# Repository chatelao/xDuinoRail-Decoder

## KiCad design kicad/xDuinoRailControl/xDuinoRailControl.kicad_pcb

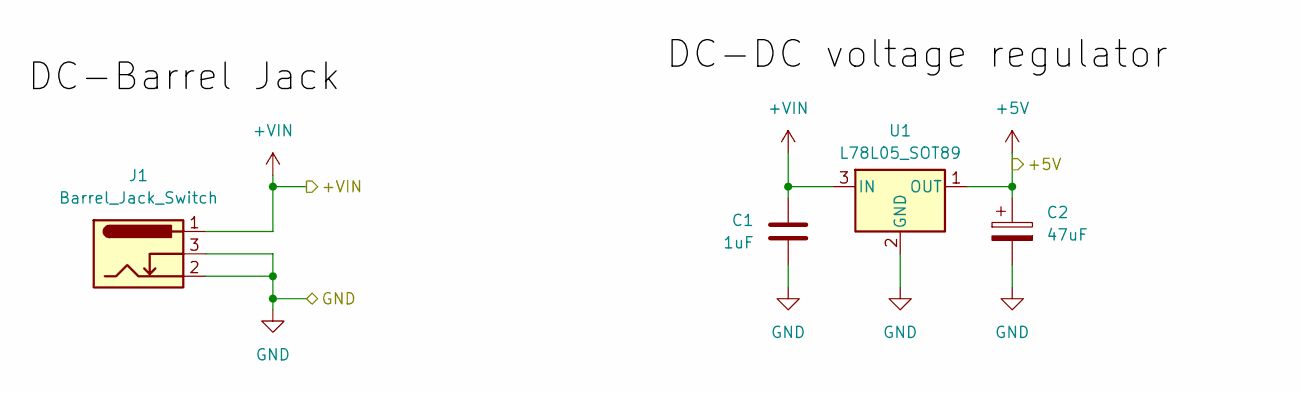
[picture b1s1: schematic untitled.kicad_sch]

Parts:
C1: 1uF; C_0805_2012Metric_Pad1.18x1.45mm_HandSolder; LCSC C28323
C2: 47uF; C_0805_2012Metric_Pad1.18x1.45mm_HandSolder; LCSC C16780
J1: Barrel_Jack_Switch; BarrelJack_Wuerth_6941xx301002; LCSC C431532
U1: L78L05_SOT89; SOT-89-3; LCSC C71136

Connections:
+3V3: C2.1, U1.1 (OUT); also elsewhere on the board
+VIN: C1.1, J1.1, U1.3 (IN); also elsewhere on the board
GND: C1.2, C2.2, J1.2, J1.3, U1.2 (GND); also elsewhere on the board

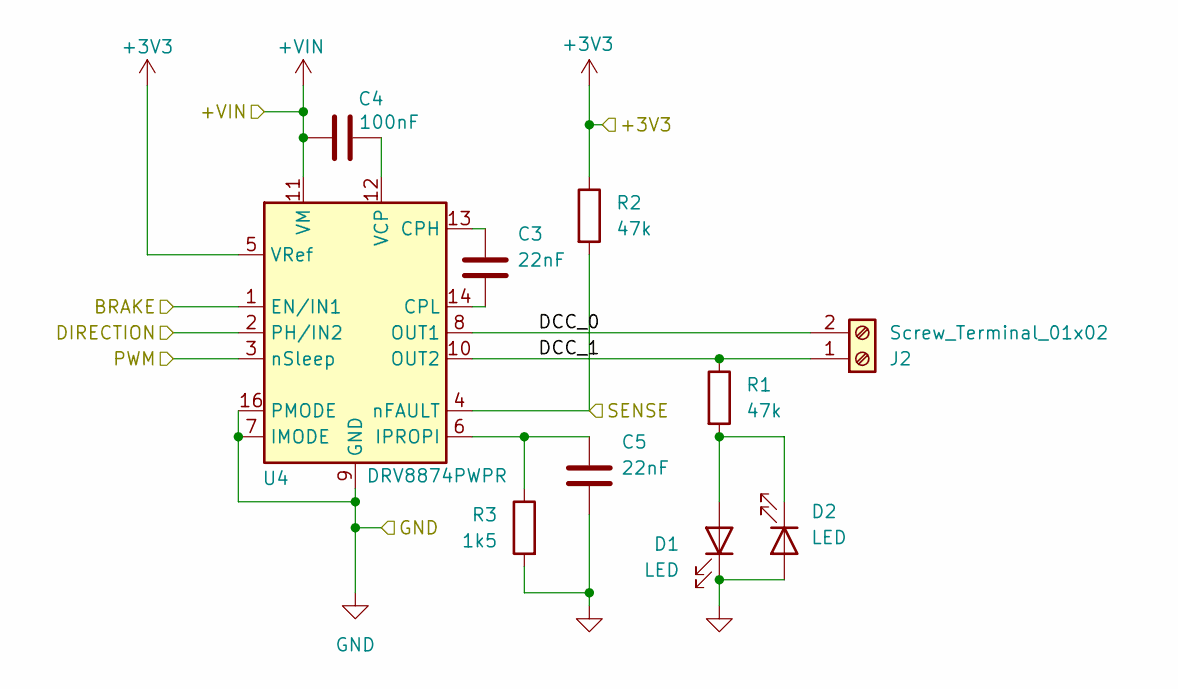
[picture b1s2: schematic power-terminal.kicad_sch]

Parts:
C3, C5: 22nF; C_0805_2012Metric_Pad1.18x1.45mm_HandSolder; LCSC C1729
C4: 100nF; C_0805_2012Metric_Pad1.18x1.45mm_HandSolder; LCSC C49678
D1, D2: LED; LED_0805_2012Metric_Pad1.15x1.40mm_HandSolder; LCSC C2296
J2: Screw_Terminal_01x02; TerminalBlock_MetzConnect_Type701_RT11L02HGLU_1x02_P6.35mm_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; LCSC C784937
R1, R2: 47k; R_0805_2012Metric_Pad1.20x1.40mm_HandSolder; LCSC C17713
R3: 1k5; R_0805_2012Metric_Pad1.20x1.40mm_HandSolder; LCSC C4310
U4: DRV8874PWPR; HTSSOP-16-1EP_4.4x5mm_P0.65mm_EP3.4x5mm_Mask2.46_HiAmp; LCSC Part # C1855818

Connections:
+3V3: R2.1, U4.5 (VRef); also elsewhere on the board
+VIN: C4.2, U4.11 (VM); also elsewhere on the board
/Control Board/BRAKE: U4.1 (EN/IN1); also elsewhere on the board
/Control Board/DIRECTION: U4.2 (PH/IN2); also elsewhere on the board
/Control Board/PWM: U4.3 (nSleep); also elsewhere on the board
/Control Board/SENSE: R2.2, U4.4 (nFAULT); also elsewhere on the board
/Power Output/DCC_0: J2.2, U4.8 (OUT1)
/Power Output/DCC_1: J2.1, R1.1, U4.10 (OUT2)
GND: C5.2, D1.1 (K), D2.2 (A), R3.2, U4.7 (IMODE), U4.9 (GND), U4.15 (GND), U4.16 (PMODE), U4.17 (GND); also elsewhere on the board
unnamed: D1.2 (A), D2.1 (K), R1.2
unnamed: C3.1, U4.13 (CPH)
unnamed: C3.2, U4.14 (CPL)
unnamed: C5.1, R3.1, U4.6 (IPROPI)
unnamed: C4.1, U4.12 (VCP)

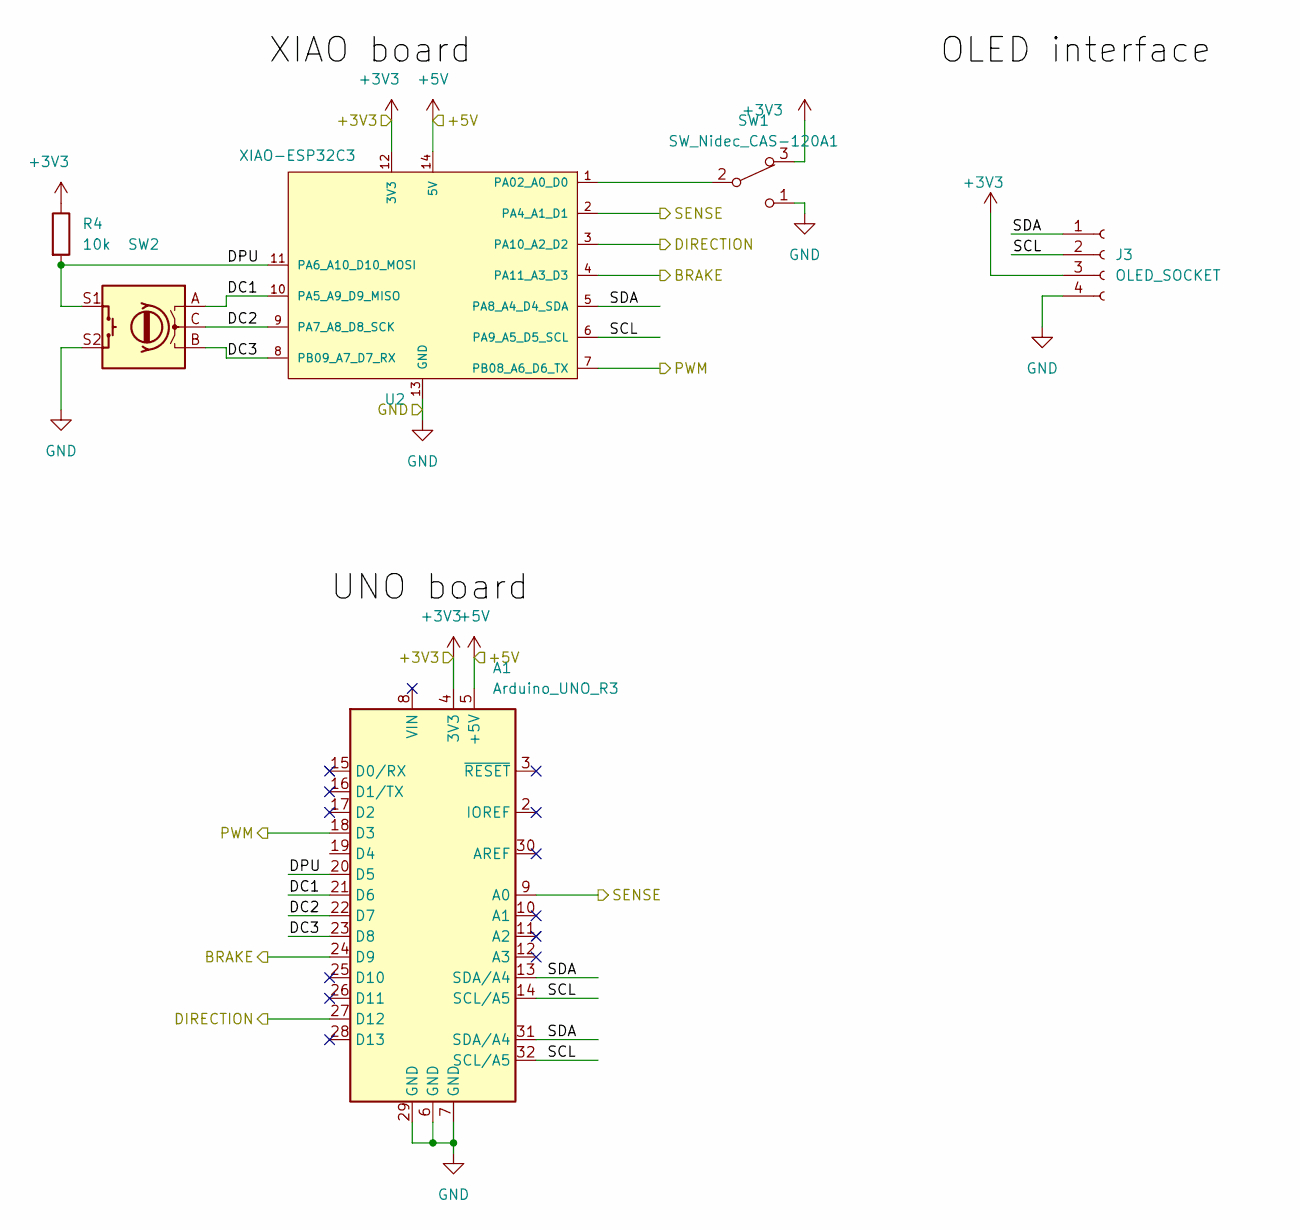
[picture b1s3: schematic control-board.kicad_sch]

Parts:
A1: Arduino_UNO_R3
J3: OLED_SOCKET; PinSocket_1x04_P2.54mm_Vertical; LCSC C2718488
R4: 10k; R_0805_2012Metric_Pad1.20x1.40mm_HandSolder
SW1: SW_Nidec_CAS-120A1; Nidec_Copal_CAS-120A; LCSC C109335
SW2: RotaryEncoder_Switch; RotaryEncoder_Alps_EC11E-Switch_Vertical_H20mm_CircularMoun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
U2: XIAO-ESP32C3; MOUDLE14P-SMD-2.54-21X17.8MM

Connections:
+3V3: A1.4 (3V3), A1.5 (+5V), J3.3, R4.1, SW1.3 (A), U2.12 (3V3), U2.14 (5V); also elsewhere on the board
/Control Board/BRAKE: A1.24 (D9), U2.4 (PA11_A3_D3); also elsewhere on the board
/Control Board/DC1: A1.21 (D6), SW2.A, U2.10 (PA5_A9_D9_MISO)
/Control Board/DC2: A1.22 (D7), SW2.C, U2.9 (PA7_A8_D8_SCK)
/Control Board/DC3: A1.23 (D8), SW2.B, U2.8 (PB09_A7_D7_RX)
/Control Board/DIRECTION: A1.27 (D12), U2.3 (PA10_A2_D2); also elsewhere on the board
/Control Board/DPU: A1.20 (D5), R4.2, SW2.S1, U2.11 (PA6_A10_D10_MOSI)
/Control Board/PWM: A1.18 (D3), U2.7 (PB08_A6_D6_TX); also elsewhere on the board
/Control Board/SCL: A1.14 (SCL/A5), A1.32 (SCL/A5), J3.2, U2.6 (PA9_A5_D5_SCL)
/Control Board/SDA: A1.13 (SDA/A4), A1.31 (SDA/A4), J3.1, U2.5 (PA8_A4_D4_SDA)
/Control Board/SENSE: A1.9 (A0), U2.2 (PA4_A1_D1); also elsewhere on the board
GND: A1.6 (GND), A1.7 (GND), A1.29 (GND), J3.4, SW1.1 (C), SW2.S2, U2.13 (GND); also elsewhere on the board
unnamed: SW1.2 (B), U2.1 (PA02_A0_D0)

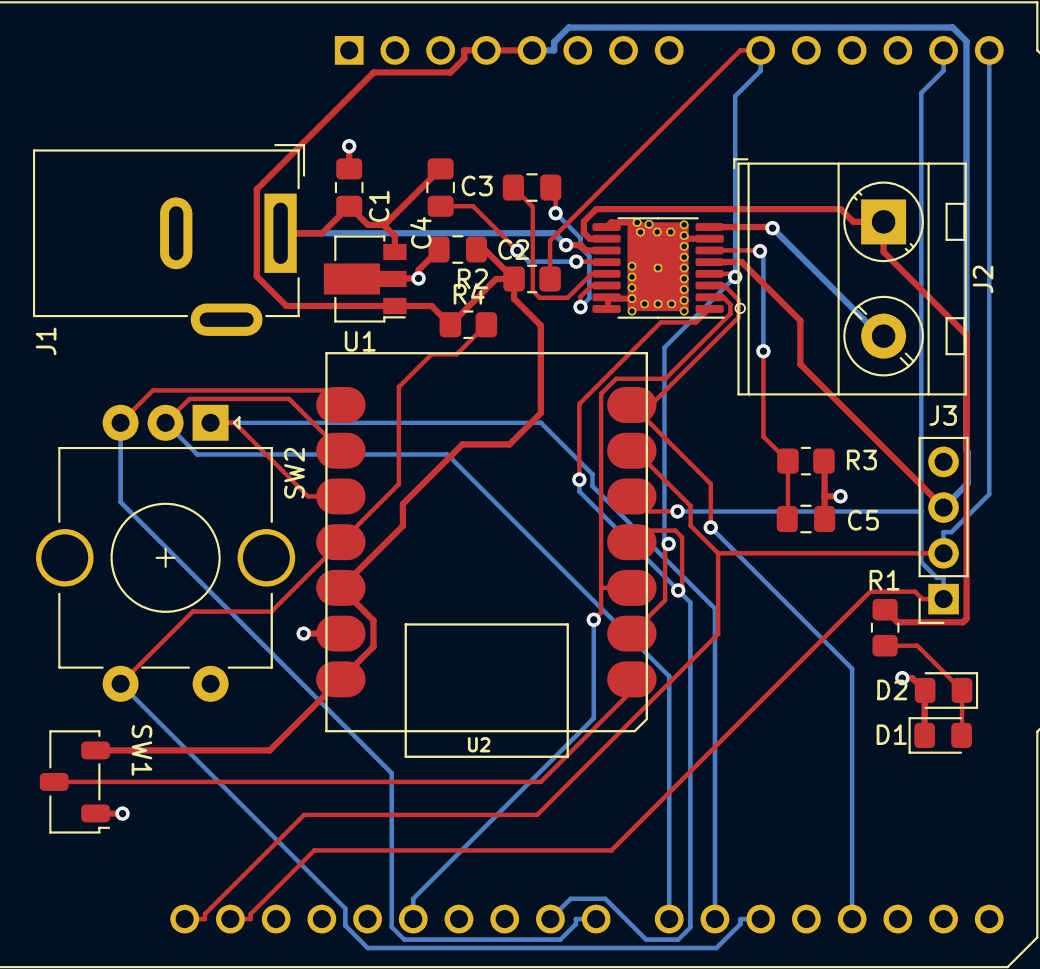
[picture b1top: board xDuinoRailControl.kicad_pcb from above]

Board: 2 copper layers, 20 parts (0 on the bottom side), 21 nets.

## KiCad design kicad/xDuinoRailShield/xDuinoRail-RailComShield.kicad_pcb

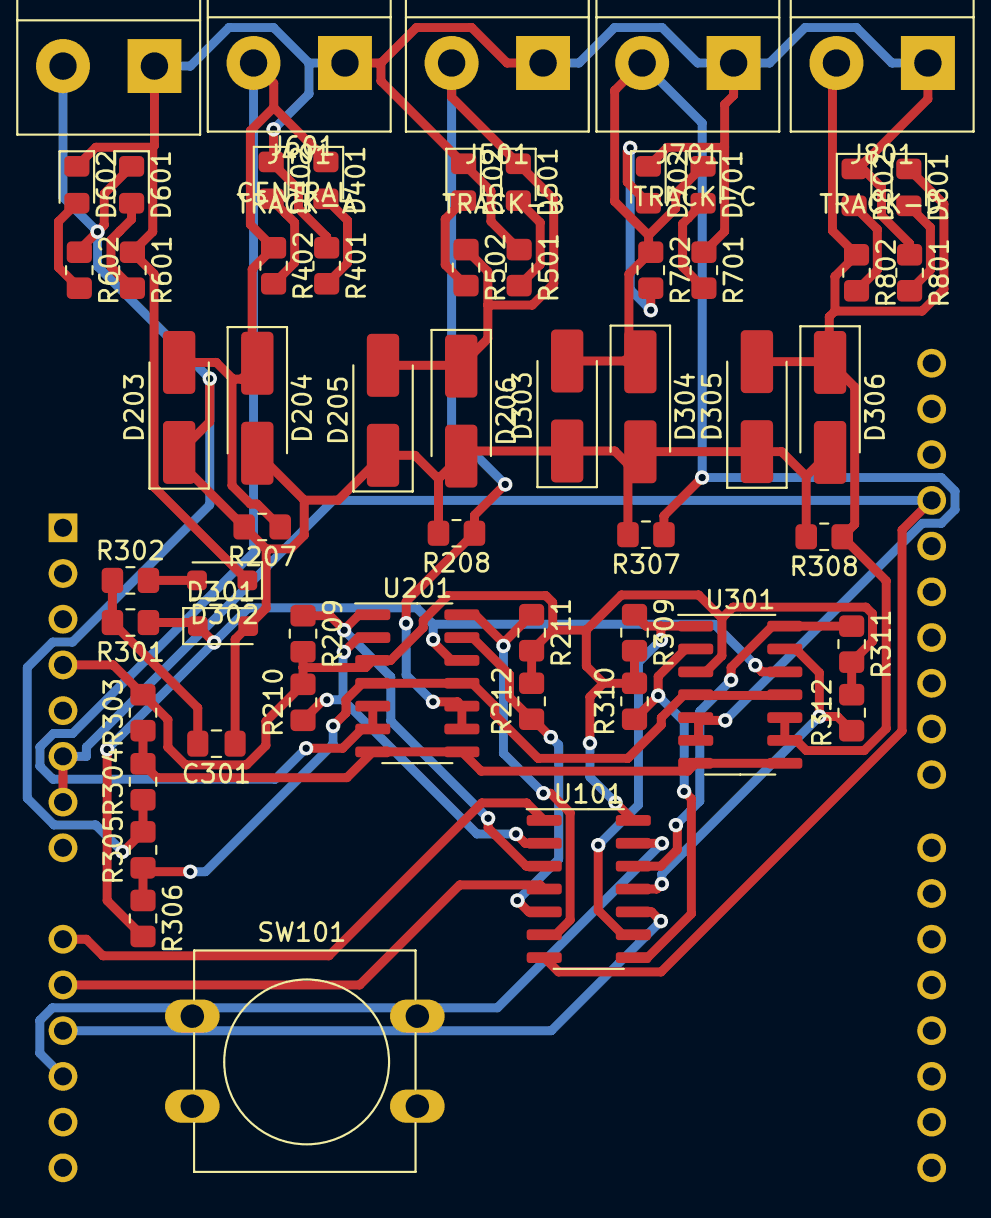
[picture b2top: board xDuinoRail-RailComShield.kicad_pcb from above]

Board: 2 copper layers, 59 parts (1 on the bottom side), 36 nets.

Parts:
A101: Arduino_UNO_R3
C301: 47uF; C_0805_2012Metric_Pad1.18x1.45mm_HandSolder
D203, D204, D205, D206, D303, D304, D305, D306: SS54; D_SMA_Handsoldering
D301, D302: 1N4004; D_SOD-123F
D401, D402, D501, D502, D601, D602, D701, D702, D801, D802: LED; LED_0805_2012Metric_Pad1.15x1.40mm_HandSolder
J401, J501, J601, J701, J801: Screw_Terminal_01x02; TerminalBlock_bornier-2_P5.08mm
R207, R208, R307, R308: 1R8; R_0805_2012Metric_Pad1.20x1.40mm_HandSolder
R209, R210, R211, R212, R309, R310, R311, R312: 10K; R_0805_2012Metric_Pad1.20x1.40mm_HandSolder
R301, R302: 220R; R_0805_2012Metric_Pad1.20x1.40mm_HandSolder
R303: 180K; R_0805_2012Metric_Pad1.20x1.40mm_HandSolder
R304: 1K; R_0805_2012Metric_Pad1.20x1.40mm_HandSolder
R305: 820R; R_0805_2012Metric_Pad1.20x1.40mm_HandSolder
R306: 33k; R_0805_2012Metric_Pad1.20x1.40mm_HandSolder
R401, R402, R501, R502, R601, R602, R701, R702, R801, R802: 3k3; R_0805_2012Metric_Pad1.20x1.40mm_HandSolder
SW101: SW_Push; SW_PUSH-12mm
U101: 74HC02; SOIC-14_3.9x8.7mm_P1.27mm
U201, U301: LM339; SOIC-14_3.9x8.7mm_P1.27mm

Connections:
+3V3: A101.4 (3V3), R209.2, R210.2, R211.2, R212.2, R303.2, R309.2, R310.2, R311.2, R312.2, U101.14 (VCC), U201.3 (V+), U301.3 (V+)
+18mV: R303.1, R304.2, U201.7 (+), U201.8 (-), U301.7 (+), U301.8 (-)
-18mv: R305.1, R306.1, U201.4 (-), U201.11 (+), U301.4 (-), U301.11 (+)
-750mv: D301.1 (K), R301.1, R306.2, U201.12 (V-), U301.12 (V-)
/DCC_CENTRAL0: C301.1, D203.1 (K), D204.2 (A), D205.1 (K), D206.2 (A), D301.2 (A), D303.1 (K), D304.2 (A), D305.1 (K), D306.2 (A), D601.1 (K), J601.2, R207.2, R208.2, R304.1, R305.2, R307.2, R308.2, R602.1
/DCC_CENTRAL1: D302.1 (K), D402.1 (K), D502.1 (K), D602.1 (K), D702.1 (K), D802.1 (K), J401.1, J501.1, J601.1, J701.1, J801.1, R401.1, R501.1, R601.1, R701.1, R801.1
/DCC_TRACK_A0: D203.2 (A), D204.1 (K), D401.1 (K), J401.2, R207.1, R402.1, U201.5 (+), U201.6 (-)
/DCC_TRACK_B0: D205.2 (A), D206.1 (K), D501.1 (K), J501.2, R208.1, R502.1, U201.9 (+), U201.10 (-)
/DCC_TRACK_C0: D303.2 (A), D304.1 (K), D701.1 (K), J701.2, R307.1, R702.1, U301.5 (+), U301.6 (-)
/DCC_TRACK_D0: D305.2 (A), D306.1 (K), D801.1 (K), J801.2, R308.1, R802.1, U301.9 (+), U301.10 (-)
/RAILCOM_A: A101.9 (A0), U101.1
/RAILCOM_A0: R210.1, U101.2, U201.2
/RAILCOM_A1: R209.1, U101.3, U201.1
/RAILCOM_B: A101.10 (A1), U101.4
/RAILCOM_B0: R212.1, U101.5, U201.13
/RAILCOM_B1: R211.1, U101.6, U201.14
/RAILCOM_C: A101.11 (A2), U101.10
/RAILCOM_C0: R310.1, U101.8, U301.2
/RAILCOM_C1: R309.1, U101.9, U301.1
/RAILCOM_D: A101.12 (A3), U101.13
/RAILCOM_D0: R312.1, U101.11, U301.13
/RAILCOM_D1: R311.1, U101.12, U301.14
/central_railcom-power-source/DCC_NEG_HALF: C301.2, R301.2, R302.1
GND: A101.6 (GND), A101.7 (GND), A101.29 (GND), SW101.1, U101.7 (GND)
unnamed: A101.3 (~RESET), SW101.2
unnamed: D302.2 (A), R302.2
unnamed: D401.2 (A), R401.2
unnamed: D402.2 (A), R402.2
unnamed: D501.2 (A), R501.2
unnamed: D502.2 (A), R502.2
unnamed: D601.2 (A), R601.2
unnamed: D602.2 (A), R602.2
unnamed: D701.2 (A), R701.2
unnamed: D702.2 (A), R702.2
unnamed: D801.2 (A), R801.2
unnamed: D802.2 (A), R802.2

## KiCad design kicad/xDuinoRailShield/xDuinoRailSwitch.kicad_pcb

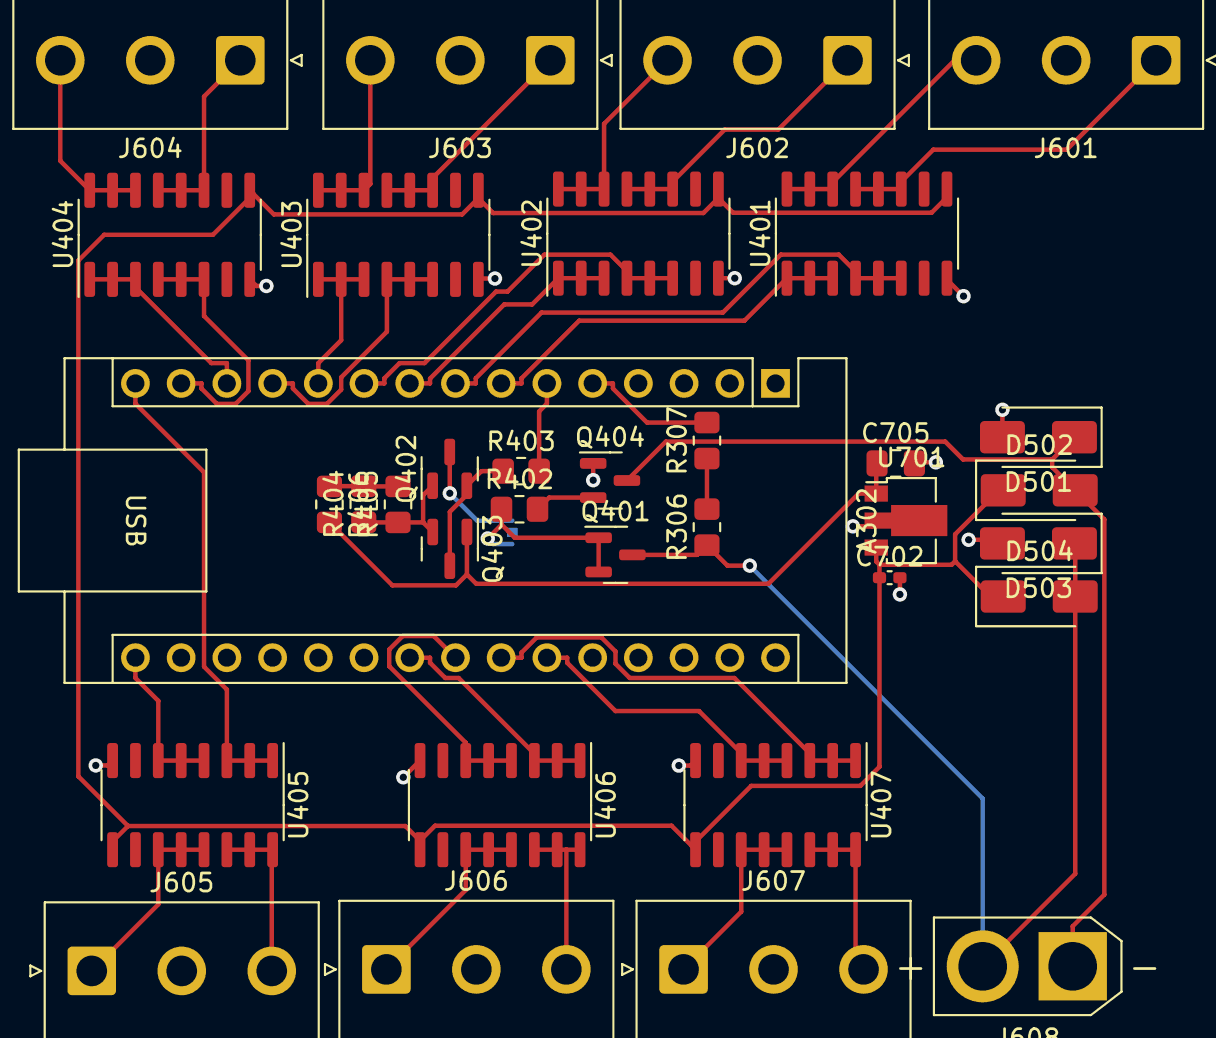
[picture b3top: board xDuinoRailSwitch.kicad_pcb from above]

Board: 2 copper layers, 35 parts (1 on the bottom side), 42 nets.

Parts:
A302: Arduino_Nano_Every; Arduino_Nano
C702: 1uF; C_0402_1005Metric_Pad0.74x0.62mm_HandSolder
C705: 47uF; C_0805_2012Metric_Pad1.18x1.45mm_HandSolder
D501, D502, D503, D504: SS54; D_SMA
J601, J602, J603, J604, J605, J606, J607: Conn_01x03; JST_NV_B03P-NV_1x03_P5.00mm_Vertical
J608: Conn_01x02; AMASS_XT30U-F_1x02_P5.0mm_Vertical
JP401: J_EnableRailcom; SolderJumper-2_P1.3mm_Bridged_RoundedPad1.0x1.5mm
Q401, Q404: S8050; SOT-23
Q402, Q403: S8550; SOT-23
R306, R307, R402, R403: 10k; R_0805_2012Metric_Pad1.20x1.40mm_HandSolder
R404, R405, R406: 10R; R_0805_2012Metric_Pad1.20x1.40mm_HandSolder
U401, U402, U403, U404, U405, U406, U407: ULN2003; SOIC-16_3.9x9.9mm_P1.27mm
U701: HT7533-1; SOT-89-3

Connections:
+3V3: C705.1, Q403.1 (E), R406.2, U701.1 (OUT)
/DCC0: D501.1 (K), D502.2 (A), J608.1, Q404.3 (C)
/DCC1: D503.1 (K), D504.2 (A), J608.2, Q401.3 (C), R306.1
/Digital Signal Extraction/DCC_MM_SIGNAL: A302.5 (D2), R307.2
/IO Carrier Switch/RAILCOM_DATA: A302.6 (D3), R403.2
/IO Carrier Switch/SW0: A302.7 (D4), U401.1 (I1), U401.2 (I2), U401.3 (I3)
/IO Carrier Switch/SW1: A302.8 (D5), U401.4 (I4), U401.5 (I5), U401.6 (I6)
/IO Carrier Switch/SW2: A302.9 (D6), U402.1 (I1), U402.2 (I2), U402.3 (I3)
/IO Carrier Switch/SW3: A302.10 (D7), U402.4 (I4), U402.5 (I5), U402.6 (I6)
/IO Carrier Switch/SW4: A302.11 (D8), U403.1 (I1), U403.2 (I2), U403.3 (I3)
/IO Carrier Switch/SW5: A302.12 (D9), U403.4 (I4), U403.5 (I5), U403.6 (I6)
/IO Carrier Switch/SW6: A302.13 (D10), U404.1 (I1), U404.2 (I2), U404.3 (I3)
/IO Carrier Switch/SW7: A302.14 (MOSI), U404.4 (I4), U404.5 (I5), U404.6 (I6)
/IO Carrier Switch/SW8: A302.15 (MISO), U405.1 (I1), U405.2 (I2), U405.3 (I3)
/IO Carrier Switch/SW9: A302.16 (SCK), U405.4 (I4), U405.5 (I5), U405.6 (I6)
/IO Carrier Switch/SW10: A302.22 (A3), U406.1 (I1), U406.2 (I2), U406.3 (I3)
/IO Carrier Switch/SW11: A302.23 (SDA/A4), U406.4 (I4), U406.5 (I5), U406.6 (I6)
/IO Carrier Switch/SW12: A302.24 (SCL/A5), U407.1 (I1), U407.2 (I2), U407.3 (I3)
/IO Carrier Switch/SW13: A302.25 (A6), U407.4 (I4), U407.5 (I5), U407.6 (I6)
/Railcom-Feedback/RC_CURR: Q402.1 (E), Q403.2 (B), R404.1, R405.1
/Railcom-Feedback/RC_FB_IN: Q402.2 (B), Q403.3 (C), R403.1
/Railcom-Feedback/RC_ON_OFF: Q404.2 (B), R402.2
/Railcom-Feedback/RC_SIGNAL: JP401.2 (B), Q401.1 (E), Q401.2 (B), R402.1
/Switch/AMP_SW0: J601.3, U401.14 (O3), U401.15 (O2), U401.16 (O1)
/Switch/AMP_SW1: J601.1, U401.11 (O6), U401.12 (O5), U401.13 (O4)
/Switch/AMP_SW2: J602.3, U402.14 (O3), U402.15 (O2), U402.16 (O1)
/Switch/AMP_SW3: J602.1, U402.11 (O6), U402.12 (O5), U402.13 (O4)
/Switch/AMP_SW4: J603.3, U403.14 (O3), U403.15 (O2), U403.16 (O1)
/Switch/AMP_SW5: J603.1, U403.11 (O6), U403.12 (O5), U403.13 (O4)
/Switch/AMP_SW6: J604.3, U404.14 (O3), U404.15 (O2), U404.16 (O1)
/Switch/AMP_SW7: J604.1, U404.11 (O6), U404.12 (O5), U404.13 (O4)
/Switch/AMP_SW8: J605.3, U405.14 (O3), U405.15 (O2), U405.16 (O1)
/Switch/AMP_SW9: J605.1, U405.11 (O6), U405.12 (O5), U405.13 (O4)
/Switch/AMP_SW10: J606.3, U406.14 (O3), U406.15 (O2), U406.16 (O1)
/Switch/AMP_SW11: J606.1, U406.11 (O6), U406.12 (O5), U406.13 (O4)
/Switch/AMP_SW12: J607.3, U407.14 (O3), U407.15 (O2), U407.16 (O1)
/Switch/AMP_SW13: J607.1, U407.11 (O6), U407.12 (O5), U407.13 (O4)
GND: A302.4 (GND), A302.29 (GND), C702.2, C705.2, D501.2 (A), D503.2 (A), Q404.1 (E), U401.8 (GND), U402.8 (GND), U403.8 (GND), U404.8 (GND), U405.8 (GND), U406.8 (GND), U407.8 (GND), U701.2 (GND)
unnamed: JP401.1 (A), Q402.3 (C)
unnamed: R306.2, R307.1
unnamed: R404.2, R405.2, R406.1
U+: C702.1, D502.1 (K), D504.1 (K), U401.9 (COM), U402.9 (COM), U403.9 (COM), U404.9 (COM), U405.9 (COM), U406.9 (COM), U407.9 (COM), U701.3 (IN)
